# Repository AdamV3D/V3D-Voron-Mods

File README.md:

# V3D-Voron-Mods
Modifications for Voron Printers by Vector 3D

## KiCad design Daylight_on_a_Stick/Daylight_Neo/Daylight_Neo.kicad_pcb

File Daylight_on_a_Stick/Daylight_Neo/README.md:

# Daylight on a stick

Chainable 24V LED bar to be used with high quality 4000K LEDs to give the illusion of daylight in your Voron.  

Ideally popuplated with 90+ CRI LEDs (3V, ~60mA), but currently LCSC does not carry those, so the BOM has 80 CRI ones. Just as bright, bit less accurate color reproduction.  
If you solder them yourself, get better leds, for example:  
[Digikey CRI90+](https://www.digikey.com/en/products/detail/JB2835AWT-W-U40GA0000-N0000001/2138-JB2835AWT-W-U40GA0000-N0000001CT-ND/10820479)  
[AliExpress CRI95+](https://www.aliexpress.com/item/4000389792048.html) (non affiliate link)

Use any angled 2.54mm(0.1") connector such as a 90 degree pinheader, angled JST-XH or Molex KK254.

## Klipper
Use the Daylight on a stick directly on 24V or hook them up to a spare heater output on your controlboard. In this last case you can control it using:

```
[output_pin daylight]
pin: ##PIN##
pwm: True
cycle_time: 0.01
```

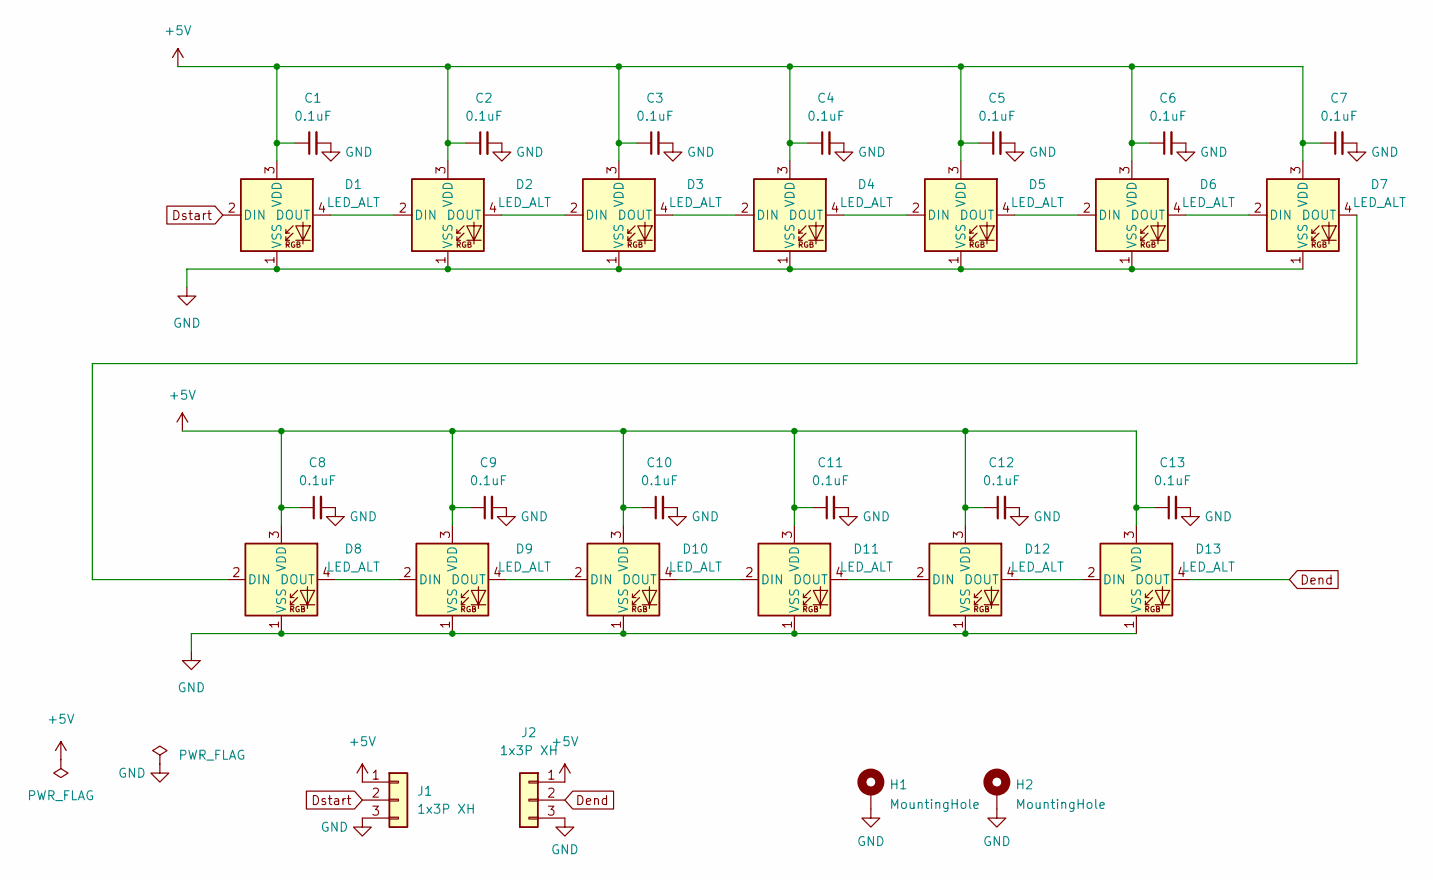
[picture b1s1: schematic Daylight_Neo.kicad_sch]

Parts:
C1, C2, C3, C4, C5, C6, C7, C8, C9, C10, C11, C12, C13: 0.1uF; C_0805_2012Metric_Pad1.18x1.45mm_HandSolder_V3Dspec; LCSC C28233
D1, D2, D3, D4, D5, D6, D7, D8, D9, D10, D11, D12, D13: LED_ALT; XL-3528RGBW-WS2812B; LCSC C2890364
H1, H2: MountingHole; MountingHole_3.2mm_M3_Pad_Via
J1, J2: 1x3P XH; JST_XH_S3B-XH-A_1x03_P2.50mm_Horizontal; LCSC C2908612

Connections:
+5V: C1.1, C2.1, C3.1, C4.1, C5.1, C6.1, C7.1, C8.1, C9.1, C10.1, C11.1, C12.1, C13.1, D1.3 (VDD), D2.3 (VDD), D3.3 (VDD), D4.3 (VDD), D5.3 (VDD), D6.3 (VDD), D7.3 (VDD), D8.3 (VDD), D9.3 (VDD), D10.3 (VDD), D11.3 (VDD), D12.3 (VDD), D13.3 (VDD), J1.1, J2.1
Dend: D13.4 (DOUT), J2.2
Dstart: D1.2 (DIN), J1.2
GND: C1.2, C2.2, C3.2, C4.2, C5.2, C6.2, C7.2, C8.2, C9.2, C10.2, C11.2, C12.2, C13.2, D1.1 (VSS), D2.1 (VSS), D3.1 (VSS), D4.1 (VSS), D5.1 (VSS), D6.1 (VSS), D7.1 (VSS), D8.1 (VSS), D9.1 (VSS), D10.1 (VSS), D11.1 (VSS), D12.1 (VSS), D13.1 (VSS), H1.1, H2.1, J1.3, J2.3
unnamed: D1.4 (DOUT), D2.2 (DIN)
unnamed: D2.4 (DOUT), D3.2 (DIN)
unnamed: D3.4 (DOUT), D4.2 (DIN)
unnamed: D4.4 (DOUT), D5.2 (DIN)
unnamed: D5.4 (DOUT), D6.2 (DIN)
unnamed: D6.4 (DOUT), D7.2 (DIN)
unnamed: D7.4 (DOUT), D8.2 (DIN)
unnamed: D8.4 (DOUT), D9.2 (DIN)
unnamed: D9.4 (DOUT), D10.2 (DIN)
unnamed: D10.4 (DOUT), D11.2 (DIN)
unnamed: D11.4 (DOUT), D12.2 (DIN)
unnamed: D12.4 (DOUT), D13.2 (DIN)

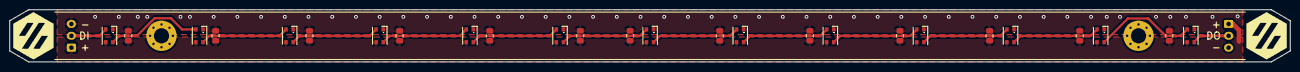
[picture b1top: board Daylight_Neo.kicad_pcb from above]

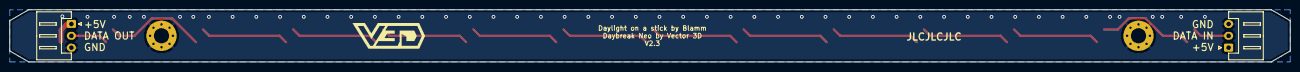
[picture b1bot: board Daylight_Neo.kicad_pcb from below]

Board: 2 copper layers, 270.0 x 11.0 mm, 30 parts (2 on the bottom side), 16 nets.

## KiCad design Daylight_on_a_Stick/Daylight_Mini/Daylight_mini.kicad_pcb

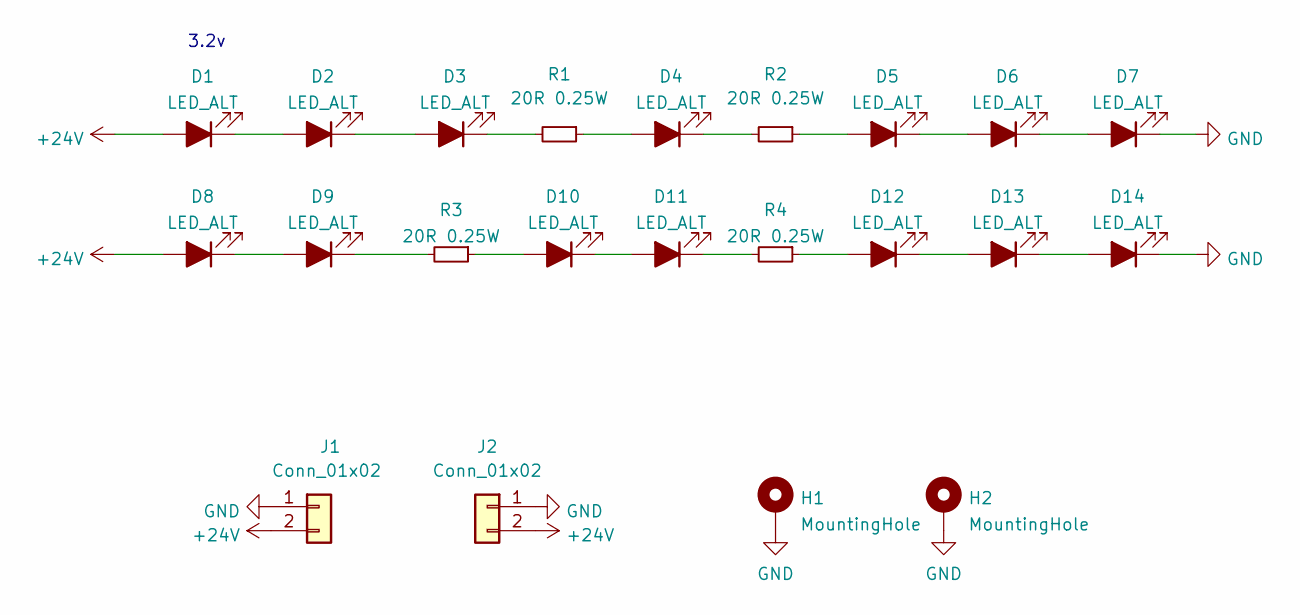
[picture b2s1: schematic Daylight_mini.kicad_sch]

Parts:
D1, D2, D3, D4, D5, D6, D7, D8, D9, D10, D11, D12, D13, D14: LED_ALT; LED_PLCC_2835; LCSC C2843876
H1, H2: MountingHole; MountingHole_3.2mm_M3_Pad_Via
J1, J2: Conn_01x02; JST_XH_S2B-XH-A_1x02_P2.50mm_Horizontal; LCSC C2908611
R1, R2, R3, R4: 20R 0.25W; R_1206_3216Metric; LCSC C17955

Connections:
+24V: D1.2 (A), D8.2 (A), J1.2, J2.2
GND: D7.1 (K), D14.1 (K), H1.1, H2.1, J1.1, J2.1
unnamed: D1.1 (K), D2.2 (A)
unnamed: D2.1 (K), D3.2 (A)
unnamed: D3.1 (K), R1.2
unnamed: D4.1 (K), R2.2
unnamed: D4.2 (A), R1.1
unnamed: D5.1 (K), D6.2 (A)
unnamed: D5.2 (A), R2.1
unnamed: D6.1 (K), D7.2 (A)
unnamed: D8.1 (K), D9.2 (A)
unnamed: D9.1 (K), R3.2
unnamed: D10.1 (K), D11.2 (A)
unnamed: D10.2 (A), R3.1
unnamed: D11.1 (K), R4.2
unnamed: D12.1 (K), D13.2 (A)
unnamed: D12.2 (A), R4.1
unnamed: D13.1 (K), D14.2 (A)

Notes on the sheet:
3.2v

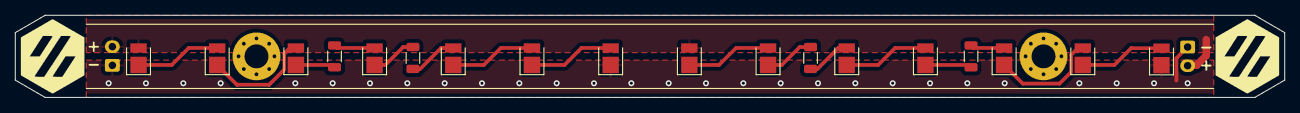
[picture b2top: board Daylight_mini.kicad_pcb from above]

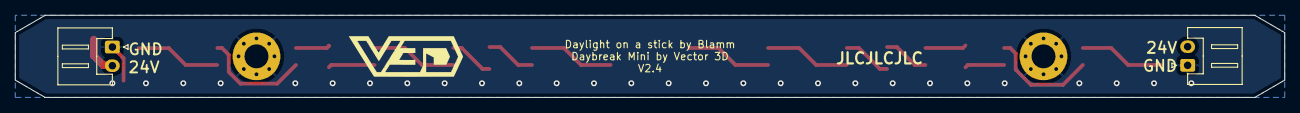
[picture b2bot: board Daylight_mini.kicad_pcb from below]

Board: 2 copper layers, 170.0 x 11.0 mm, 22 parts (2 on the bottom side), 18 nets.

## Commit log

2021-12-14 My Printer Config File Added
2022-01-26 Organised Mods and Added Custom Upgrades
2022-02-11 Corners with pins added
2022-06-17 Added Folders For Mods + New Mods
    Added UHP Power Supple DIN Rail Cross Mount.
    Added Daylight on a Stick
2022-06-17 Stick Mount Improved
2022-06-28 Smart Filament Sensor Mount Added
2022-07-21 Daylight Standard, Mini and Neo Versions Added in New Repo
    Daylight on a stick a.k.a Daylight
    Daylight mini (170mm version of Daylight)
    Daylight Neo (Neopixel version of Daylight)
    Daylight Neo Mini (Neopixel version of Daylight Mini)
2022-07-22 Fixed some Layout LED footprint issues
2022-08-15 Added V0 Config File
    Added V0 Config File
2022-08-17 Daylight (all) V2.2
    The JST XH silkscreen did not match the connectors very well so it has been adjusted.
    Added small front silkscreen to indicate pins
    Adjusted one connector on day_mini that was misplaced 1mm.
2022-08-20 Daybreak Mounts Added
2022-08-22 Daybreak Mount that fits Neo Size JST
2022-08-22 Mounts for v2.4 With Baffles
    Compatible with Daybreak, Daybreak Neo, and their mini versions but not compatible with v0.
2022-08-25 V2.4 R2 Wiring Diagram and Firmware Added
2022-08-25 Added Baffle Mount Images
2022-09-07 V2 Mount for baffles added
2022-09-07 Mellow Fly Pi Mount and Insert DIN Clips Added
2022-10-19 Minor Updates
2022-12-01 Added EBB36 Mount
2022-12-01 Minor LED Updates
2023-03-21 More Mods added
2023-05-03 mount updates
2025-01-25 bracket removed
